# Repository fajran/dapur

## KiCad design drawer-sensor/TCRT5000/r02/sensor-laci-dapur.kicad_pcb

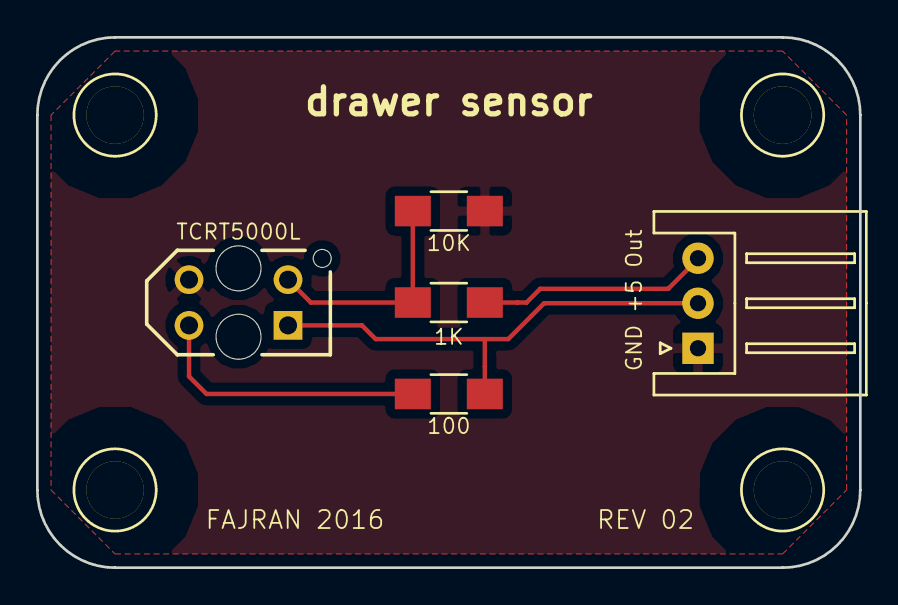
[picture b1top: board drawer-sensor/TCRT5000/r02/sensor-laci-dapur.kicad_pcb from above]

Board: 2 copper layers, 45.7 x 29.5 mm, 6 parts (0 on the bottom side), 5 nets.

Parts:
M: 1pin
R1: 10K; R_1206_HandSoldering
R2: 1K; R_1206_HandSoldering
R3: 100; R_1206_HandSoldering
Sensor1: TCRT5000L; XDCR_TCRT5000L
U1: 1_Out; JST_XH_S03B-XH-A_03x2.50mm_Angled

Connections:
+5V: R3.1, Sensor1.1, U1.2
/Out: R2.1, U1.3
GND: R1.2, Sensor1.3, U1.1
unnamed: R1.1, R2.2, Sensor1.2
unnamed: R3.2, Sensor1.4

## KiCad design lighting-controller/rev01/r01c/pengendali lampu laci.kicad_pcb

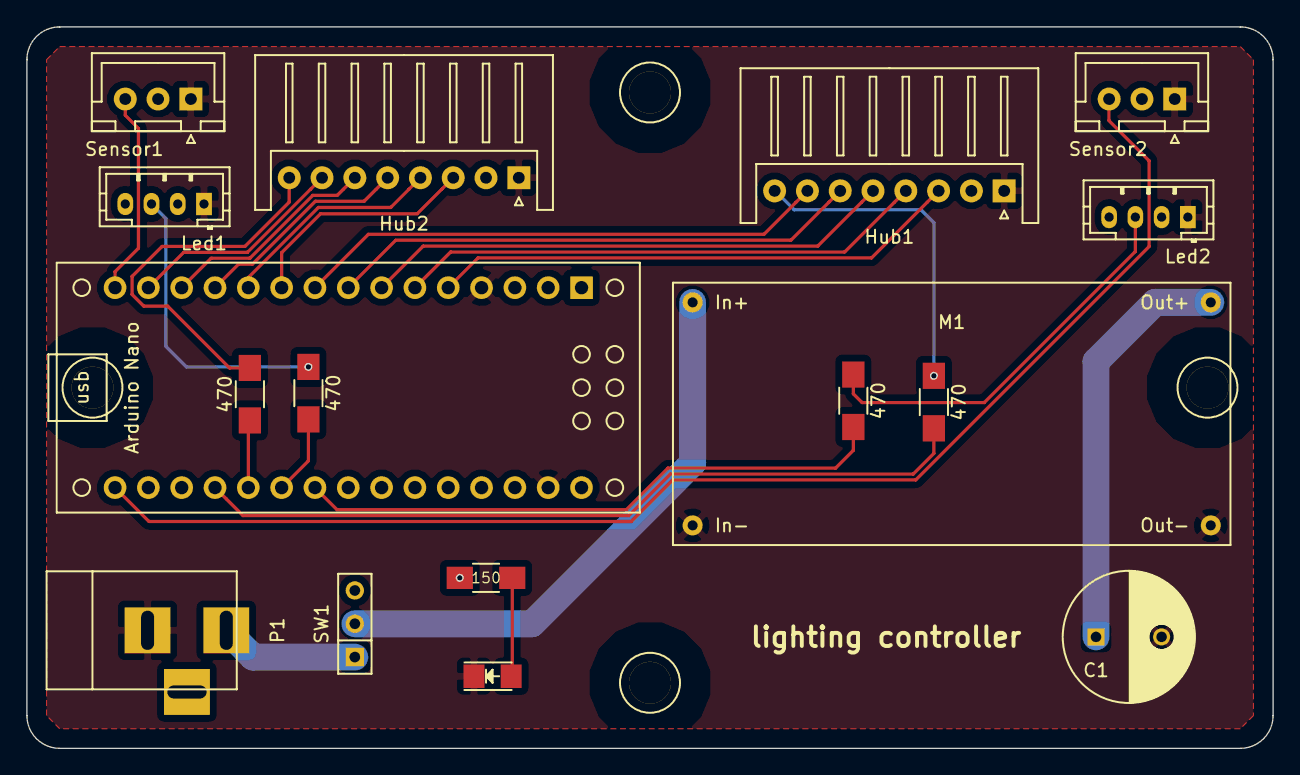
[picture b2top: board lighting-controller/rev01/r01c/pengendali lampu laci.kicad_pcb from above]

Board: 2 copper layers, 95.0 x 55.0 mm, 17 parts (0 on the bottom side), 25 nets.

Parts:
Arduino1: Arduino Nano; Arduino Nano Shield
C1: CP; C_Radial_D10_L20_P5
D1: LED; LED_1206
Hub1, Hub2: Cabinet Hub; JST_XH_S08B-XH-A_08x2.50mm_Angled
Led1, Led2: Led; JST_PH_B4B-PH-K_04x2.00mm_Straight
M1: LM2596_Module
P1: Power; BARREL_JACK
R1, R2, R3, R4: 470; R_1206_HandSoldering
R5: 150; R_1206_HandSoldering
SW1: SPST; SW_Micro_SPST
Sensor1, Sensor2: Sensor; JST_XH_B03B-XH-A_03x2.50mm_Straight

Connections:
+5V: Arduino1.27, C1.1, Hub1.2, Hub2.2, Led1.2, Led2.2, M1.3, R5.2, Sensor1.2, Sensor2.2
/In1: Arduino1.5, Hub1.3
/In2: Arduino1.6, Hub1.4
/In3: Arduino1.7, Hub1.5
/In4: Arduino1.8, Hub1.6
/In5: Arduino1.9, Hub1.7
/In6: Arduino1.10, Hub2.3
/In7: Arduino1.11, Hub2.4
/In8: Arduino1.12, Hub2.5
/In9: Arduino1.13, Hub2.6
/In10: Arduino1.14, Hub2.7
/In11: Arduino1.15, Sensor1.3
/In12: Arduino1.16, Sensor2.3
/Out1: Arduino1.19, R1.1
/Out2: Arduino1.20, R2.1
/Out3: Arduino1.21, R3.1
/Out4: Arduino1.22, R4.1
/Vin: P1.1, SW1.1
GND: Arduino1.4, Arduino1.29, C1.2, D1.1, Hub1.1, Hub2.1, Led1.1, Led2.1, M1.2, M1.4, P1.2, Sensor1.1, Sensor2.1
unnamed: D1.2, R5.1
unnamed: Hub1.8, R1.2
unnamed: Hub2.8, R2.2
unnamed: Led1.3, R3.2
unnamed: Led2.3, R4.2
VCC: M1.1, SW1.2

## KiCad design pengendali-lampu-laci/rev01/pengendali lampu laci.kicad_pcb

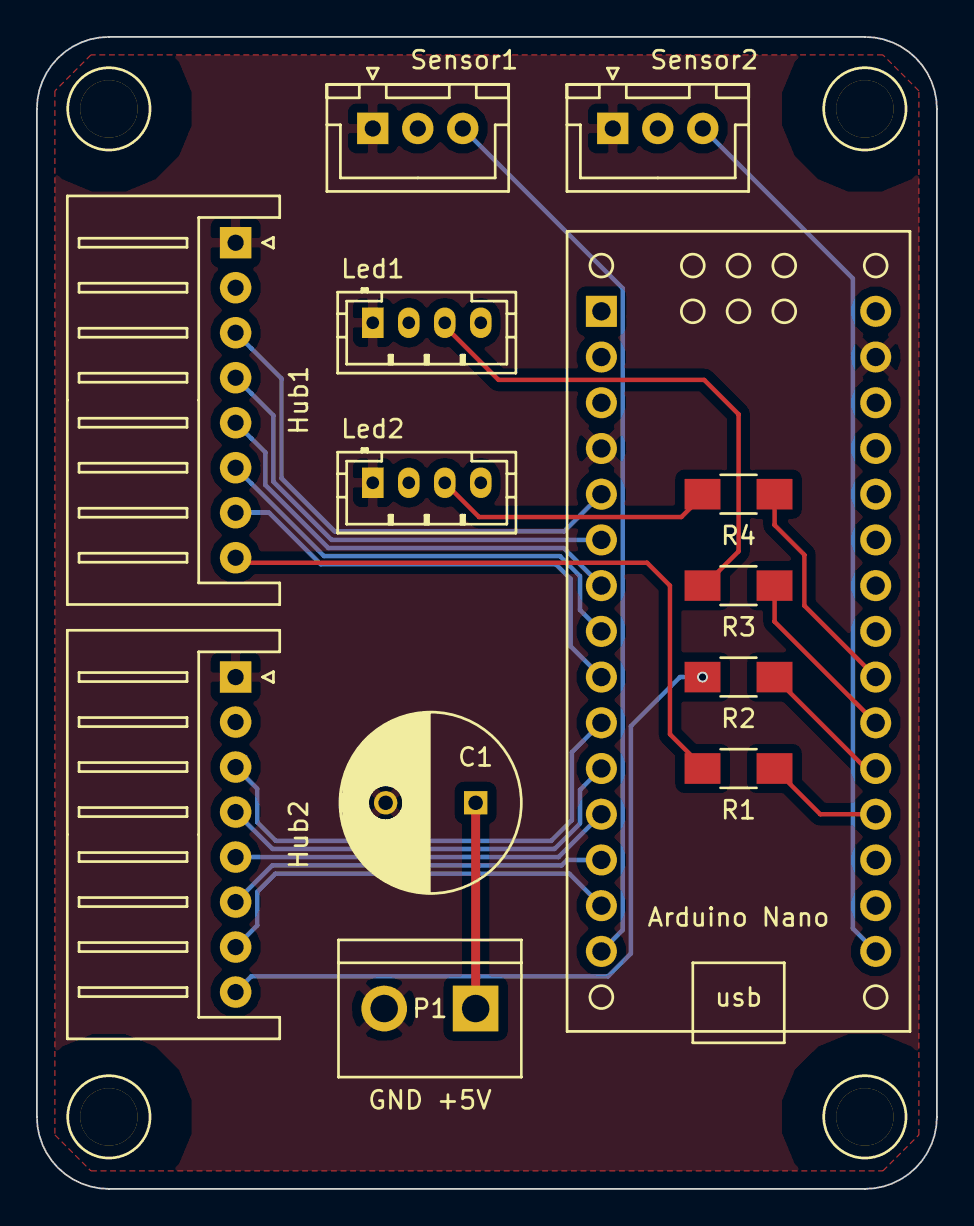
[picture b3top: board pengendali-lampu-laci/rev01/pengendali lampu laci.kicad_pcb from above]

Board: 2 copper layers, 50.0 x 64.0 mm, 13 parts (0 on the bottom side), 22 nets.

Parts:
Arduino Nano: Arduino Nano; Arduino Nano Shield
C1: CP; C_Radial_D10_L20_P5
Hub1, Hub2: Cabinet Hub; JST_XH_S08B-XH-A_08x2.50mm_Angled
Led1, Led2: Led; JST_PH_B4B-PH-K_04x2.00mm_Straight
P1: Power; bornier2
R1, R2, R3, R4: 470; R_1206_HandSoldering
Sensor1, Sensor2: Sensor; JST_XH_B03B-XH-A_03x2.50mm_Straight

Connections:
+5V: Arduino Nano.27, C1.1, Hub1.2, Hub2.2, Led1.2, Led2.2, P1.1, Sensor1.2, Sensor2.2
/In1: Arduino Nano.5, Hub1.3
/In2: Arduino Nano.6, Hub1.4
/In3: Arduino Nano.7, Hub1.5
/In4: Arduino Nano.8, Hub1.6
/In5: Arduino Nano.9, Hub1.7
/In6: Arduino Nano.10, Hub2.3
/In7: Arduino Nano.11, Hub2.4
/In8: Arduino Nano.12, Hub2.5
/In9: Arduino Nano.13, Hub2.6
/In10: Arduino Nano.14, Hub2.7
/In11: Arduino Nano.15, Sensor1.3
/In12: Arduino Nano.16, Sensor2.3
/Out1: Arduino Nano.19, R1.1
/Out2: Arduino Nano.20, R2.1
/Out3: Arduino Nano.21, R3.1
/Out4: Arduino Nano.22, R4.1
GND: Arduino Nano.4, Arduino Nano.29, C1.2, Hub1.1, Hub2.1, Led1.1, Led2.1, P1.2, Sensor1.1, Sensor2.1
unnamed: Hub1.8, R1.2
unnamed: Hub2.8, R2.2
unnamed: Led1.3, R3.2
unnamed: Led2.3, R4.2

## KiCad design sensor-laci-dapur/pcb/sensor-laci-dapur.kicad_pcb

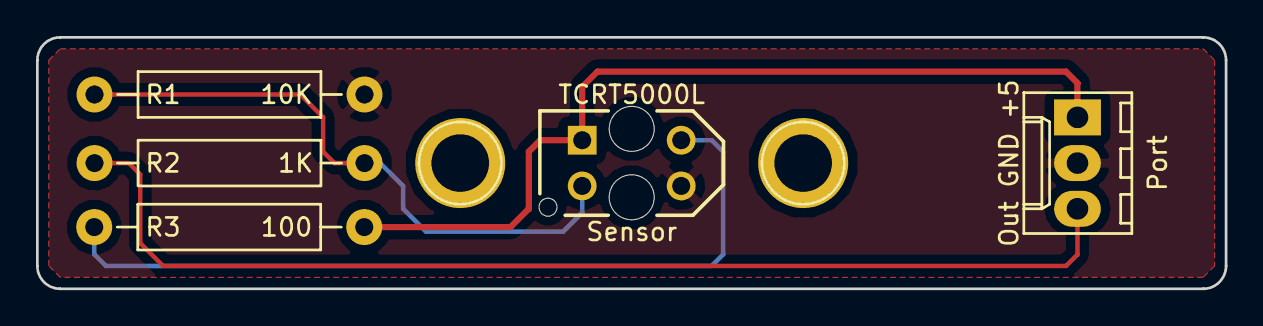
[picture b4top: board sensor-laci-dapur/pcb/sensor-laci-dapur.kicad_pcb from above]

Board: 2 copper layers, 66.0 x 14.0 mm, 5 parts (0 on the bottom side), 5 nets.

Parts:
Port: Out GND +5; Molex_KK-6410-03_03x2.54mm_Straight
R1: 10K; Resistor_Horizontal_RM15mm
R2: 1K; Resistor_Horizontal_RM15mm
R3: 100; Resistor_Horizontal_RM15mm
Sensor: TCRT5000L; XDCR_TCRT5000L

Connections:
unnamed: Port.1, R3.1, Sensor.1
unnamed: Port.2, R1.2, Sensor.3
unnamed: Port.3, R2.1
unnamed: R1.1, R2.2, Sensor.2
unnamed: R3.2, Sensor.4
